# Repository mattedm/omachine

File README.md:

# omachine

The omachine is a linear-rail machine driven by an ODrive S1, controlled by a handheld haptic
handle. Move the handle and the carriage follows. You can also set it running one of 19 stroke
patterns, with the handle showing the speed, length and stroke on its round display. Both boards
are ESP32-S3s, linked wirelessly over ESP-NOW.

This repository has everything: the firmware for both boards, the handle's circuit boards
(KiCad) and the mechanical design (FreeCAD).

## What's here

```
controller/     firmware: the machine's controller (ESP32-S3 dev board, CAN to the ODrive S1)
manipulator/    firmware: the handle (ESP32-S3, DRV8311 gimbal motor driver, display, knob, button)
hardware/
  pcb/
    manipulator/       the handle's main board (KiCad 9)
    encoder-breakouts/ the handle's magnetic and rotary encoder boards (KiCad 9)
  cad/
    manipulator/       the handle (FreeCAD)
    machine/           the main machine (FreeCAD)
docs/           the stroke graph
```

## How it works

- **Start-up.** The controller brings the ODrive into closed loop. It then homes by driving the
  carriage slowly into each end of the rail, and sets the stroke's span just inside them. The
  handle finds its own end stops the same way.
- **Manual.** The carriage follows the handle, updated about 200 times a second. When the
  handle isn't being held, the carriage goes soft so it can be pushed by hand, and the handle's
  motor follows it; it stiffens again once the handle leads.
- **Auto.** The main button switches between Manual and the selected stroke. Pressing the knob
  steps through Speed, Length and Stroke, and turning it changes them. Holding the knob opens
  the menu: Power (the motor's current limit), Save settings (as the start-up defaults),
  Calibrate motor (the handle's), Set up ODrive, Wi-Fi setup and Update firmware.
- **Faults.** If the ODrive stops, the handle shows why ("Supply voltage low", for example),
  what to check and the supply voltage. The controller retries a few times; after that, the
  main button retries.

## Getting started

The FreeCAD files are stored with [Git LFS](https://git-lfs.com/), so install it before cloning:

```
git lfs install
git clone https://github.com/mattedm/omachine.git
```

`controller/` and `manipulator/` are separate ESP-IDF (v6.1) projects. Build and flash each one
from its own folder (`idf.py build`, then `idf.py -p <port> flash`); see each project's README.
In VS Code, open `omachine.code-workspace` rather than the repository folder, so that
IntelliSense uses each project's own build settings.

The two boards talk using `omachine_protocol.h`. Each project has its own copy, and the two
must stay identical. Boards on different protocol versions ignore each other, so always update
both together.

## Firmware updates

After the first flash over USB, both boards update over the air from the handle's
**Update firmware** menu item. It downloads `manipulator.bin` and `controller.bin` from this
repository's latest release, installs its own, and passes the controller's image on over
ESP-NOW. To make a release, tag the repository (e.g. `v1.4`), run
`manipulator/tools/make_release.sh` with ESP-IDF activated, and attach both images to a GitHub
release (the script shows the `gh release create` line).

## The ODrive

The ODrive S1's configuration is in [`controller/odrive/`](controller/odrive). The handle's
**Set up ODrive** menu item writes it to the ODrive over CAN, calibrates the motor (including
anticogging) and saves it. Power 100% is 40 A and the top speed is 15 turns/s. Battery draw is
capped at 20 A, and the ODrive trips below 19 V; both are set for a 6S battery with a 25 A BMS.

## Changing the strokes

Each stroke is a function in [`controller/main/strokes.c`](controller/main/strokes.c). The top
of [`strokes.h`](controller/main/strokes.h) explains how to change one or add a new one. The
handle gets the stroke names from the controller, so only the controller changes.

## Hardware

See [`hardware/`](hardware) for the circuit boards (with the files to order them from JLCPCB)
and the FreeCAD models.

## License

Copyright 2026 MattEdm.

- **Firmware** (`controller/`, `manipulator/`): GPL-3.0-or-later. See [LICENSE](LICENSE). Some
  files carry their own notices; see each project's README.
- **Hardware** (`hardware/`): CERN-OHL-S-2.0. See [hardware/LICENSE](hardware/LICENSE).

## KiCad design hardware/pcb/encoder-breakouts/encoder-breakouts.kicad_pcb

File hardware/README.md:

# omachine hardware

The physical design of the omachine: the circuit board (KiCad) and the mechanical parts (FreeCAD). The firmware is in [`controller/`](../controller) and [`manipulator/`](../manipulator).

| Folder | What | Tool |
|---|---|---|
| [`pcb/manipulator/`](pcb/manipulator) | The handle's board: ESP32-S3-MINI-1, DRV8311 gimbal motor driver, 1S battery charger, connectors for the display, encoder, knob and button | KiCad 9 |
| [`pcb/encoder-breakouts/`](pcb/encoder-breakouts) | The handle's two small boards, on one breakaway panel: the MT6701 magnetic encoder (the handle motor's angle) and the EC11 rotary encoder (the knob) | KiCad 9 |
| [`cad/manipulator/`](cad/manipulator) | The handle: `manipulator.FCStd` | FreeCAD 1.1 |
| [`cad/machine/`](cad/machine) | The main machine: `omachine.FCStd` | FreeCAD 1.1 |

The FreeCAD files are stored with [Git LFS](https://git-lfs.com/). Install it (and run
`git lfs install` once) before cloning, or the `.FCStd` files arrive as small text pointers
instead of models; in a clone made without it, `git lfs pull` fetches them.

## The manipulator board

Open `pcb/manipulator/omachine-manipulator.kicad_pro` in KiCad 9. Its own footprint (USB-C) and
symbols (`jlcpcb.kicad_sym`) are in the project; nearly all 3D models are embedded in the board file.

`pcb/manipulator/production/` has the files to order the current revision from JLCPCB, made with
the Fabrication Toolkit plugin: `omachine_Manipulator_Board_1.2.zip` (Gerbers and drill files),
`bom.csv` and `positions.csv` (for assembly). After changing the board, make them again from the
plugin, so they match.

### Revision 1.2

- R19 and R21 (the main button's sense transistor, Q1) are 10k, not 100k. With 100k, a few
  microamps of leakage from D1 when the board was warm turned Q1 on, and the button read as held.
- Named the omachine manipulator board (was a DRV8311 breakout), with the source link
  github.com/mattedm/omachine on the back silkscreen.

## The encoder boards

Open `pcb/encoder-breakouts/encoder-breakouts.kicad_pro`. The two boards are separate sheets
(`encoder.kicad_sch`, `rotary.kicad_sch`) laid out on one panel with a breakaway rail, and are
ordered together from `pcb/encoder-breakouts/production/` (revision 1.0). They plug into the
manipulator board's ENCODER and ROTARY connectors.

## License

Copyright 2026 MattEdm. The hardware designs in this folder are licensed under the CERN Open
Hardware Licence Version 2 - Strongly Reciprocal (CERN-OHL-S-2.0): see [LICENSE](LICENSE). The
source location is https://github.com/mattedm/omachine. The firmware is under the GPL; see the
top-level [README](../README.md).

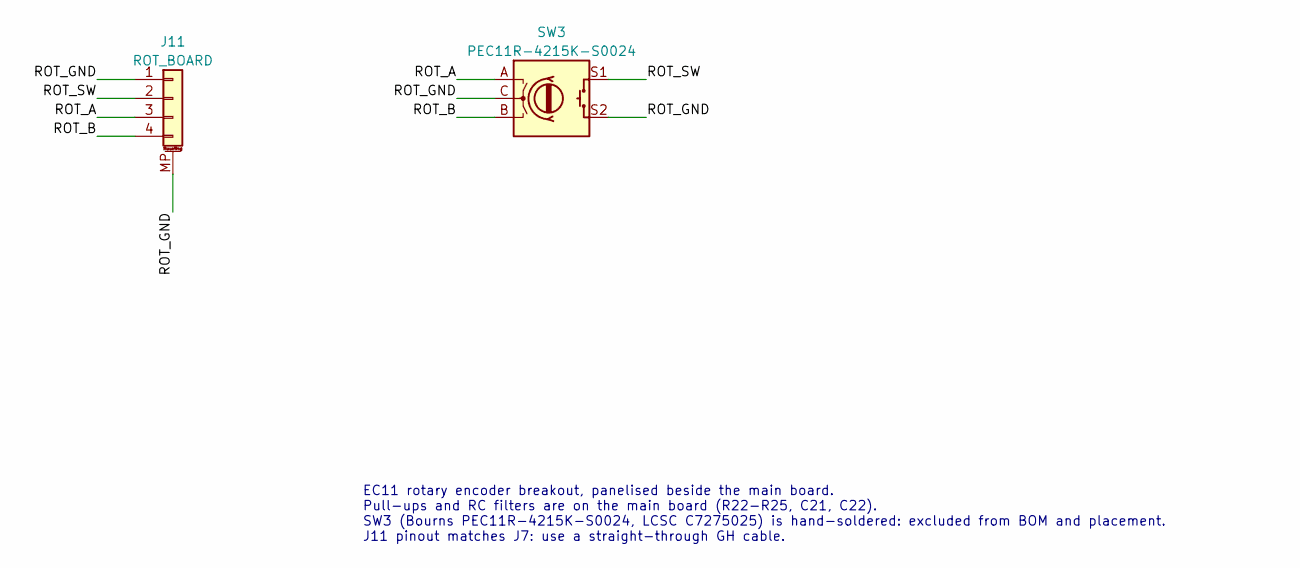
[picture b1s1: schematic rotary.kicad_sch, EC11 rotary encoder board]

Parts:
J11: ROT_BOARD; JST_GH_SM04B-GHS-TB_1x04-1MP_P1.25mm_Horizontal; LCSC Part C51940118
SW3: PEC11R-4215K-S0024; SW-TH_PEC11R-4215K-S0024; LCSC Part C7275025

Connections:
/Rotary/ROT_A: J11.3, SW3.A
/Rotary/ROT_B: J11.4, SW3.B
/Rotary/ROT_GND: J11.1, J11.MP (MountPin), SW3.C, SW3.S2
/Rotary/ROT_SW: J11.2, SW3.S1

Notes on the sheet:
EC11 rotary encoder breakout, panelised beside the main board. Pull-ups and RC filters are on the main board (R22-R25, C21, C22). SW3 (Bourns PEC11R-4215K-S0024, LCSC C7275025) is hand-soldered: excluded from BOM and placement. J11 pinout matches J7: use a straight-through GH cable.

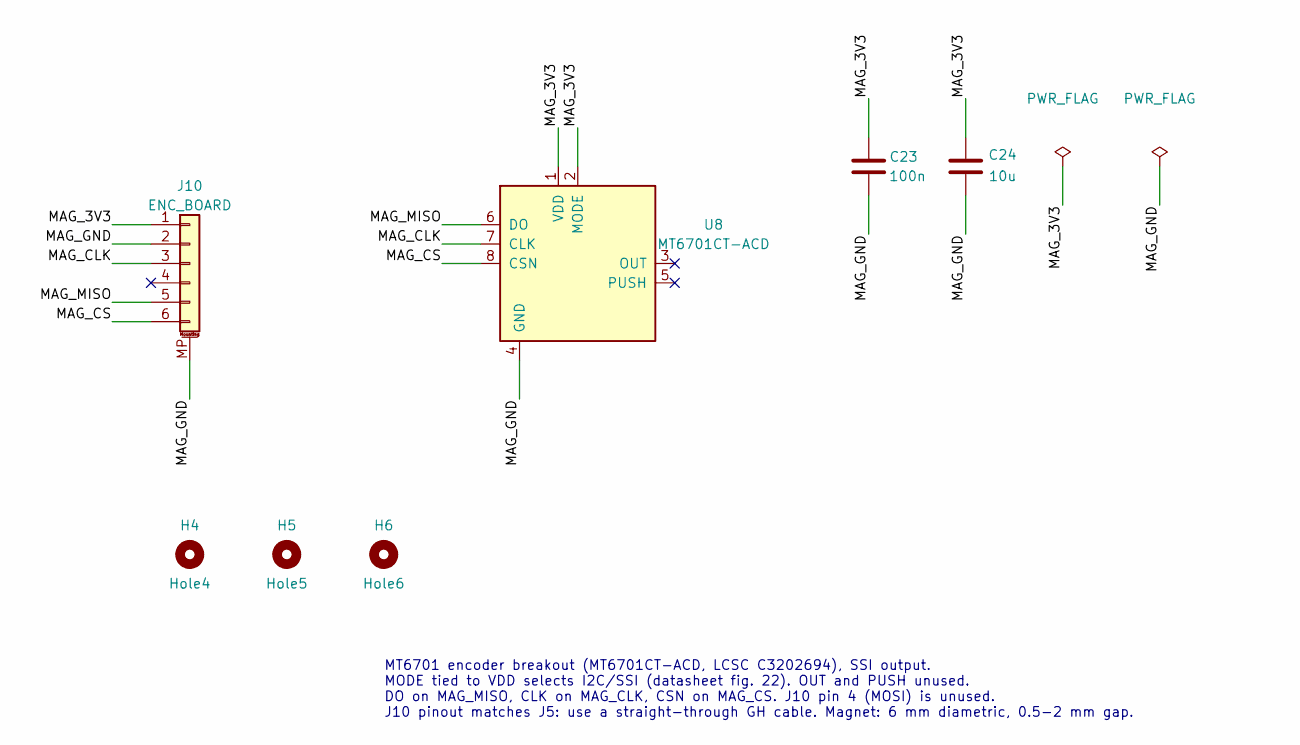
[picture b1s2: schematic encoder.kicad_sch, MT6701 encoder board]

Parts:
C23: 100n; C_0402_1005Metric; LCSC Part C1525
C24: 10u; C_0603_1608Metric; LCSC Part C19702
H4: Hole4; MountingHole_2.1mm_M2_ButtonHead
H5: Hole5; MountingHole_2.1mm_M2_ButtonHead
H6: Hole6; MountingHole_2.1mm_M2_ButtonHead
J10: ENC_BOARD; JST_GH_SM06B-GHS-TB_1x06-1MP_P1.25mm_Horizontal; LCSC Part C388711
U8: MT6701CT-ACD; SOIC-8_3.9x4.9mm_P1.27mm; LCSC Part C3202694

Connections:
/Encoder/MAG_3V3: C23.1, C24.1, J10.1, U8.1 (VDD), U8.2 (MODE)
/Encoder/MAG_CLK: J10.3, U8.7 (CLK)
/Encoder/MAG_CS: J10.6, U8.8 (CSN)
/Encoder/MAG_GND: C23.2, C24.2, J10.2, J10.MP (MountPin), U8.4 (GND)
/Encoder/MAG_MISO: J10.5, U8.6 (DO)

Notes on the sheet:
MT6701 encoder breakout (MT6701CT-ACD, LCSC C3202694), SSI output. MODE tied to VDD selects I2C/SSI (datasheet fig. 22). OUT and PUSH unused. DO on MAG_MISO, CLK on MAG_CLK, CSN on MAG_CS. J10 pin 4 (MOSI) is unused. J10 pinout matches J5: use a straight-through GH cable. Magnet: 6 mm diametric, 0.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

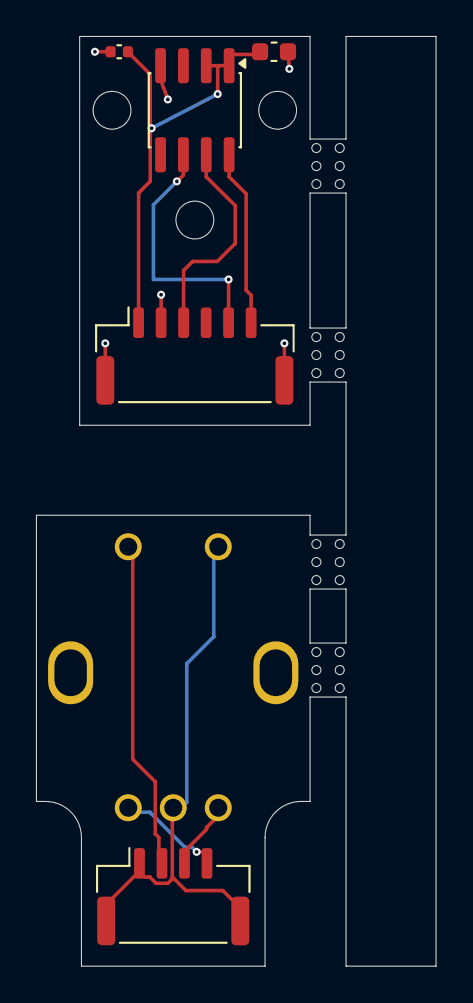
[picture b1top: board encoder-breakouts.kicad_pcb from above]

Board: 2 copper layers, 22.2 x 51.7 mm, 13 parts (1 on the bottom side), 9 nets.

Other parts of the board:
MB1, MB2, MB3, MB4: mousebite

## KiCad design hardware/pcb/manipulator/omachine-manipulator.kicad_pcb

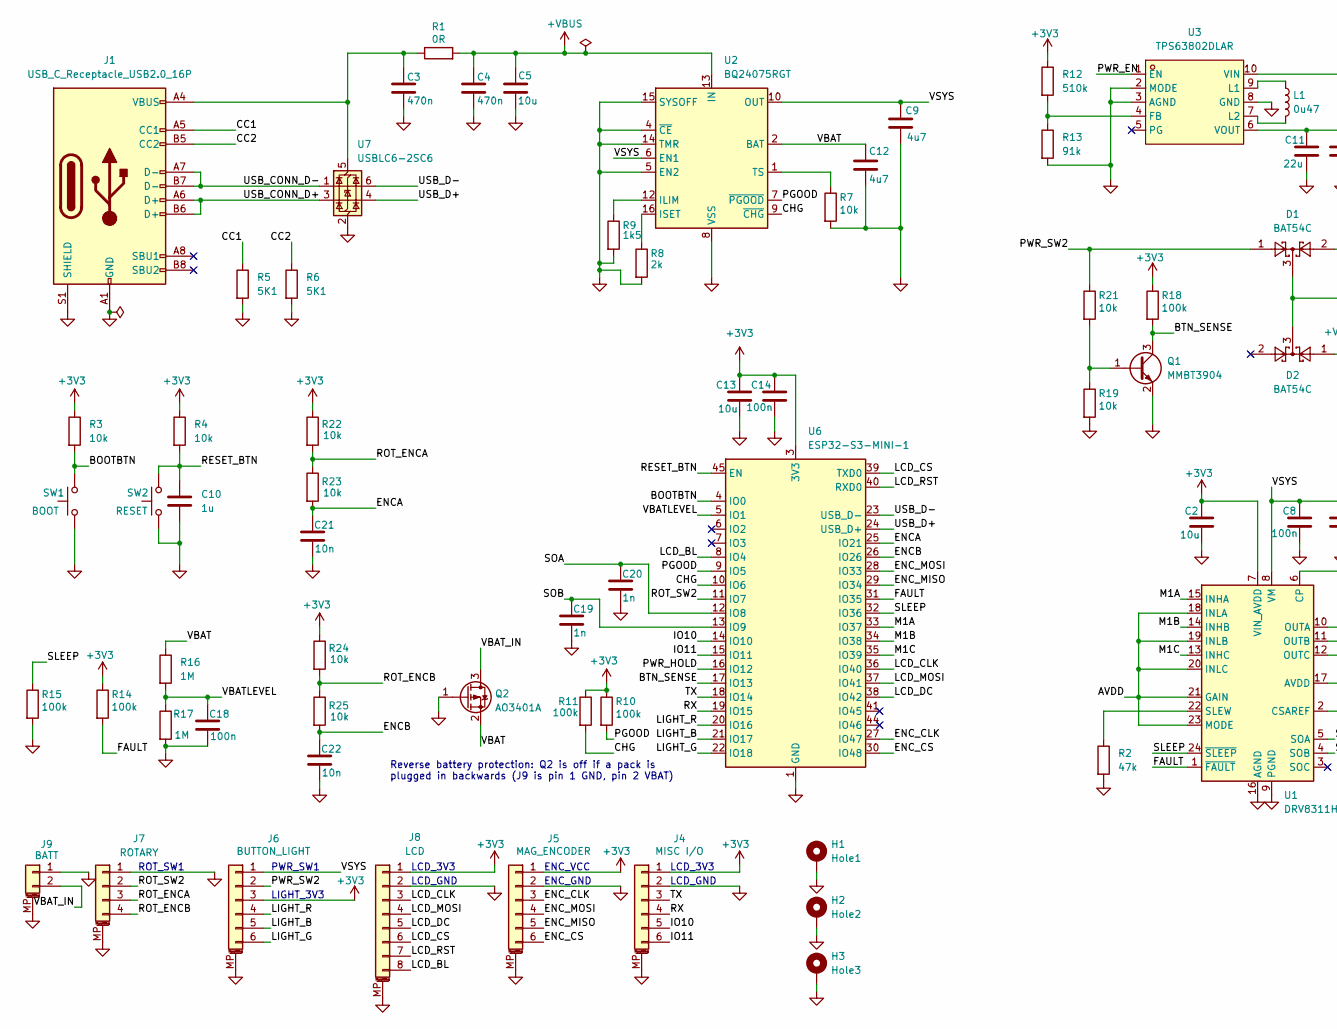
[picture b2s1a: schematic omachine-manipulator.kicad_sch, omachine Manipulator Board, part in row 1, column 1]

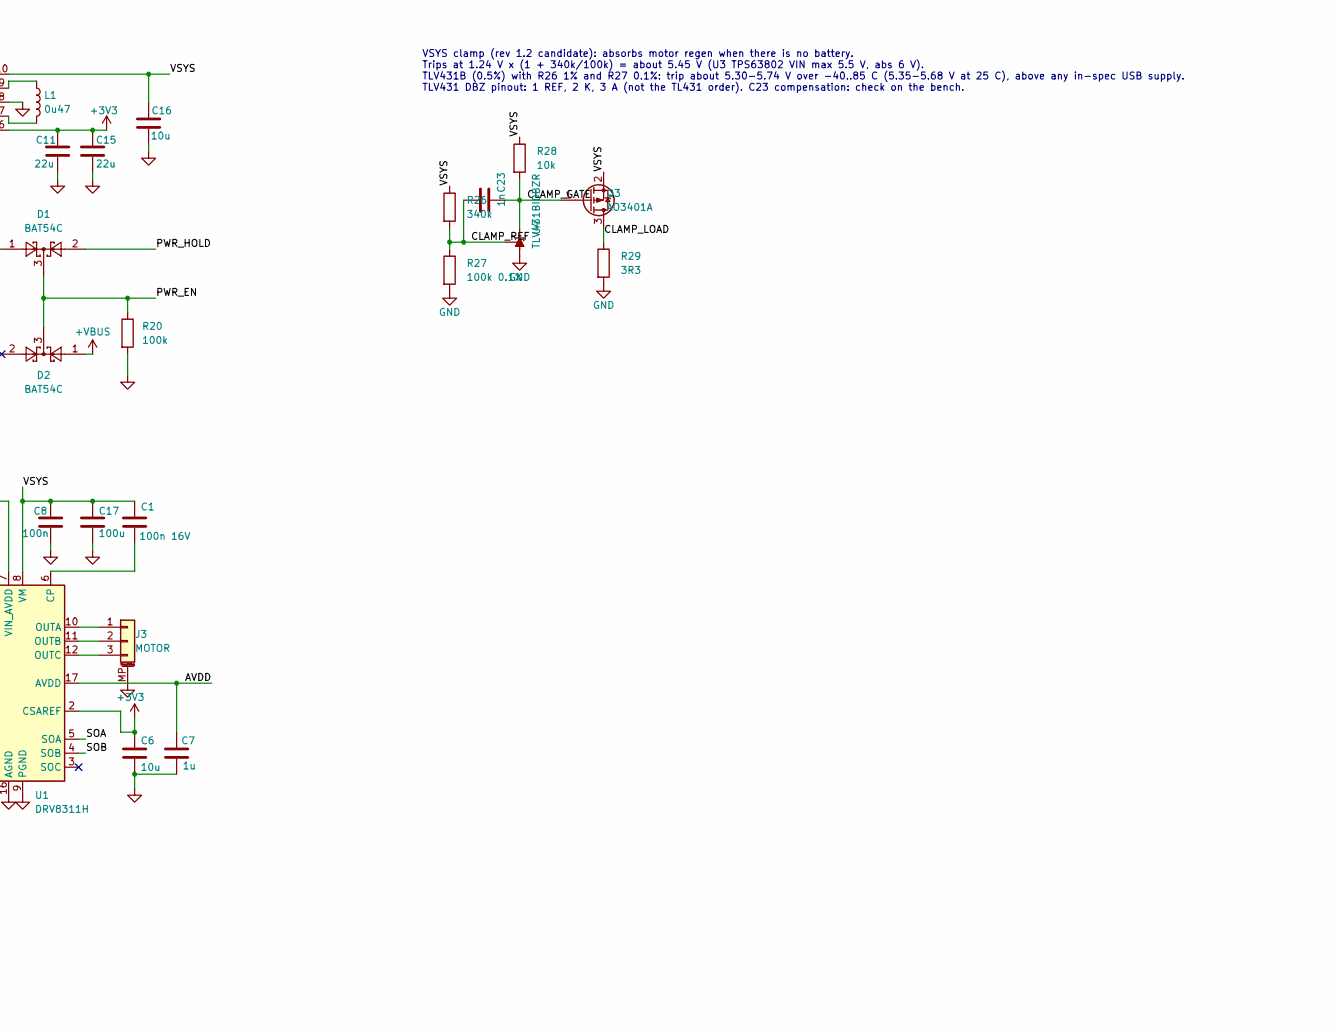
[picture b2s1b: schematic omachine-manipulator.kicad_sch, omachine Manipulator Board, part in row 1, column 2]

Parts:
C1: 100n 16V; C_0402_1005Metric; Manufacturer Part Number CL05B104KO5NNNC; LCSC Part C1525
C2, C5, C6, C13, C16: 10u; C_0805_2012Metric; Manufacturer Part Number CL21A106KAYNNNE; LCSC Part C15850
C3, C4: 470n; C_0402_1005Metric; Manufacturer Part Number CL05A474KP5NNNC; LCSC Part C47339
C7, C10: 1u; C_0402_1005Metric; Manufacturer Part Number CL05A105KA5NQNC; LCSC Part C52923
C8, C14, C18: 100n; C_0402_1005Metric; Manufacturer Part Number CL05B104KO5NNNC; LCSC Part C1525
C9, C12: 4u7; C_0603_1608Metric; Manufacturer Part Number CL10A475KO8NNNC; LCSC Part C19666
C11, C15: 22u; C_0805_2012Metric; Manufacturer Part Number CL21A226MAQNNNE; LCSC Part C45783
C17: 100u; C_1206_3216Metric; Manufacturer Part Number CL31A107MQHNNNE; LCSC Part C15008
C19, C20, C23: 1n; C_0402_1005Metric; Manufacturer Part Number 0402B102K500NT; LCSC Part C1523
C21, C22: 10n; C_0402_1005Metric; Manufacturer Part Number CL05B103KB5NNNC; LCSC Part C15195
D1, D2: BAT54C; SOT-23; Manufacturer Part Number BAT54C,215; LCSC Part C37704
H1: Hole1; MountingHole_2.2mm_M2_Pad
H2: Hole2; MountingHole_2.2mm_M2_Pad
H3: Hole3; MountingHole_2.2mm_M2_Pad
J1: USB_C_Receptacle_USB2.0_16P; USB_C_Receptacle_SHOU_HAN_TYPE-C-16PIN-2MD-073_Horizontal; Manufacturer Part Number TYPE-C 16PIN 2MD(073); LCSC Part C2765186
J3: MOTOR; JST_PH_S3B-PH-SM4-TB_1x03-1MP_P2.00mm_Horizontal; Manufacturer Part Number S3B-PH-SM4-TB(LF)(SN); LCSC Part C265101
J4: MISC I/O; JST_GH_SM06B-GHS-TB_1x06-1MP_P1.25mm_Horizontal; Manufacturer Part Number X1251WRS-06HF-LPSW; LCSC Part C388711
J5: MAG_ENCODER; JST_GH_SM06B-GHS-TB_1x06-1MP_P1.25mm_Horizontal; Manufacturer Part Number X1251WRS-06HF-LPSW; LCSC Part C388711
J6: BUTTON_LIGHT; JST_GH_SM06B-GHS-TB_1x06-1MP_P1.25mm_Horizontal; Manufacturer Part Number X1251WRS-06HF-LPSW; LCSC Part C388711
J7: ROTARY; JST_GH_SM04B-GHS-TB_1x04-1MP_P1.25mm_Horizontal; Manufacturer Part Number XY-SM04B-GHS-TB; LCSC Part C51940118
J8: LCD; JST_GH_SM08B-GHS-TB_1x08-1MP_P1.25mm_Horizontal; Manufacturer Part Number X1251WRS-08HF-LPSW; LCSC Part C388713
J9: BATT; JST_PH_B2B-PH-SM4-TB_1x02-1MP_P2.00mm_Vertical; Manufacturer Part Number B2B-PH-SM4-TB(LF)(SN); LCSC Part C160352
L1: 0u47; L_Changjiang_FNR4015S; Manufacturer Part Number FNR4018SR47NT; LCSC Part C167799
Q1: MMBT3904; SOT-23; Manufacturer Part Number MMBT3904(RANGE:100-300); LCSC Part C20526
Q2, Q3: AO3401A; SOT-23; Manufacturer Part Number AO3401A; LCSC Part C15127
R1: 0R; R_0402_1005Metric; Manufacturer Part Number 0402WGF0000TCE; LCSC Part C17168
R2: 47k; R_0402_1005Metric; Manufacturer Part Number 0402WGF4702TCE; LCSC Part C25792
R3, R4, R7, R19, R21, R22, R23, R24, R25, R28: 10k; R_0402_1005Metric; Manufacturer Part Number 0402WGF1002TCE; LCSC Part C25744
R5, R6: 5K1; R_0402_1005Metric; Manufacturer Part Number 0402WGF5101TCE; LCSC Part C25905
R8: 2k; R_0402_1005Metric; Manufacturer Part Number 0402WGF2001TCE; LCSC Part C4109
R9: 1k5; R_0402_1005Metric; Manufacturer Part Number 0402WGF1501TCE; LCSC Part C25867
R10, R11, R14, R15, R18, R20: 100k; R_0402_1005Metric; Manufacturer Part Number 0402WGF1003TCE; LCSC Part C25741
R12: 510k; R_0402_1005Metric; Manufacturer Part Number 0402WGF5103TCE; LCSC Part C11616
R13: 91k; R_0402_1005Metric; Manufacturer Part Number FRC0402F9102TS; LCSC Part C2909393
R16, R17: 1M; R_0402_1005Metric; Manufacturer Part Number 0402WGF1004TCE; LCSC Part C26083
R26: 340k; R_0402_1005Metric; Manufacturer Part Number AC0402FR-07340KL; LCSC Part C227001
R27: 100k 0.1%; R_0402_1005Metric; Manufacturer Part Number RT0402BRD07100KL; LCSC Part C852472
R29: 3R3; R_0805_2012Metric; Manufacturer Part Number 0805W8J033JT5E; LCSC Part C24787
SW1: BOOT; SW_Push_1P1T_XKB_TS-1187A; Manufacturer Part Number TS-1187A-B-A-B; LCSC Part C318884
SW2: RESET; SW_Push_1P1T_XKB_TS-1187A; Manufacturer Part Number TS-1187A-B-A-B; LCSC Part C318884
U1: DRV8311H; Texas_RRW0024A_WQFN-24-1EP_3x3mm_P0.4mm_EP1.9x1.9mm; Manufacturer Part Number DRV8311HRRWR; LCSC Part C5218862
U2: BQ24075RGT; VQFN-16-1EP_3x3mm_P0.5mm_EP1.6x1.6mm; Manufacturer Part Number BQ24075RGTR; LCSC Part C15464
U3: TPS63802DLAR; VSON-10_L3.0-W2.0-P0.50-TL; MPN TPS63802DLAR; LCSC Part C2845237
U4: TLV431BIDBZR; SOT-23; Manufacturer Part Number TLV431BIDBZR; LCSC Part C398375
U6: ESP32-S3-MINI-1; ESP32-S2-MINI-1; Manufacturer Part Number ESP32-S3-MINI-1-N8; LCSC Part C2913206
U7: USBLC6-2SC6; SOT-23-6; Manufacturer Part Number USBLC6-2SC6; LCSC Part C7519

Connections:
+3V3: C2.1, C6.1, C11.1, C13.1, C14.1, C15.1, J4.1, J5.1, J6.3, J8.1, R3.1, R4.1, R10.1, R11.1, R12.1, R14.1, R18.1, R22.1, R24.1, U1.2 (CSAREF), U1.7 (VIN_AVDD), U3.6 (VOUT), U6.3 (3V3)
+VBUS: C4.1, C5.1, D2.1, R1.2, U2.13 (IN)
/BOOTBTN: R3.2, SW1.2, U6.4 (IO0)
/BTN_SENSE: Q1.3 (C), R18.2, U6.17 (IO13)
/CC1: J1.A5 (CC1), R5.1
/CC2: J1.B5 (CC2), R6.1
/CHG: R11.2, U2.9 (~CHG), U6.10 (IO6)
/CLAMP_GATE: C23.2, Q3.1 (G), R28.2, U4.2 (K)
/CLAMP_LOAD: Q3.3 (D), R29.1
/CLAMP_REF: C23.1, R26.2, R27.1, U4.1 (REF)
/ENCA: C21.1, R23.2, U6.25 (IO21)
/ENCB: C22.1, R25.2, U6.26 (IO26)
/ENC_CLK: J5.3, U6.27 (IO47)
/ENC_CS: J5.6, U6.30 (IO48)
/ENC_MISO: J5.5, U6.29 (IO34)
/ENC_MOSI: J5.4, U6.28 (IO33)
/FAULT: R14.2, U1.1 (~FAULT), U6.31 (IO35)
/IO10: J4.5, U6.14 (IO10)
/IO11: J4.6, U6.15 (IO11)
/LCD_BL: J8.8, U6.8 (IO4)
/LCD_CLK: J8.3, U6.36 (IO40)
/LCD_CS: J8.6, U6.39 (TXD0)
/LCD_DC: J8.5, U6.38 (IO42)
/LCD_MOSI: J8.4, U6.37 (IO41)
/LCD_RST: J8.7, U6.40 (RXD0)
/LIGHT_B: J6.5, U6.21 (IO17)
/LIGHT_G: J6.6, U6.22 (IO18)
/LIGHT_R: J6.4, U6.20 (IO16)
/M1A: U1.15 (INHA), U6.33 (IO37)
/M1B: U1.14 (INHB), U6.34 (IO38)
/M1C: U1.13 (INHC), U6.35 (IO39)
/PGOOD: R10.2, U2.7 (~PGOOD), U6.9 (IO5)
/PWR_EN: D1.3, D2.3, R20.1, U3.1 (EN)
/PWR_HOLD: D1.2, U6.16 (IO12)
/PWR_SW2: D1.1, J6.2, R21.1
/RESET_BTN: C10.1, R4.2, SW2.2, U6.45 (EN)
/ROT_ENCA: J7.3, R22.2, R23.1
/ROT_ENCB: J7.4, R24.2, R25.1
/ROT_SW2: J7.2, U6.11 (IO7)
/RX: J4.4, U6.19 (IO15)
/SLEEP: R15.1, U1.24 (~SLEEP), U6.32 (IO36)
/SOA: C20.1, U1.5 (SOA), U6.12 (IO8)
/SOB: C19.1, U1.4 (SOB), U6.13 (IO9)
/TX: J4.3, U6.18 (IO14)
/USB_CONN_D+: J1.A6 (D+), J1.B6 (D+), U7.3 (I/O2)
/USB_CONN_D-: J1.A7 (D-), J1.B7 (D-), U7.1 (I/O1)
/USB_D+: U6.24 (USB_D+), U7.4 (I/O2)
/USB_D-: U6.23 (USB_D-), U7.6 (I/O1)
/VBAT: C12.2, Q2.2 (E), R16.1, U2.2 (BAT), U2.3 (BAT)
/VBATLEVEL: C18.1, R16.2, R17.1, U6.5 (IO1)
/VBAT_IN: J9.2, Q2.3 (C)
/VSYS: C1.1, C8.1, C9.2, C16.1, C17.1, J6.1, Q3.2 (S), R26.1, R28.1, U1.8 (VM), U2.6 (EN1), U2.10 (OUT), U2.11 (OUT), U3.10 (VIN)
unnamed: J3.1, U1.10 (OUTA)
unnamed: J3.2, U1.11 (OUTB)
unnamed: J3.3, U1.12 (OUTC)
unnamed: Q1.1 (B), R19.1, R21.2
unnamed: C1.2, U1.6 (CP)
unnamed: R2.1, U1.22 (SLEW)
unnamed: R9.1, U2.12 (ILIM)
unnamed: R8.1, U2.16 (ISET)
unnamed: R7.1, U2.1 (TS)
unnamed: R12.2, R13.1, U3.4 (FB)
unnamed: L1.1, U3.9 (L1)
unnamed: L1.2, U3.7 (L2)
unnamed: C3.1, J1.A4 (VBUS), J1.A9 (VBUS), J1.B4 (VBUS), J1.B9 (VBUS), R1.1, U7.5 (VBUS)

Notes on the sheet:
LIGHT_3V3
ENC_GND
ENC_VCC
PWR_SW1
LCD_3V3
LCD_GND
ROT_SW1
Reverse battery protection: Q2 is off if a pack is plugged in backwards (J9 is pin 1 GND, pin 2 VBAT)
VSYS clamp (rev 1.2 candidate): absorbs motor regen when there is no battery. Trips at 1.24 V x (1 + 340k/100k) = about 5.45 V (U3 TPS63802 VIN max 5.5 V, abs 6 V). TLV431B (0.5%) with R26 1% and R27 0.1%: trip about 5.30-5.74 V over -40..85 C (5.35-5.68 V at 25 C), above any in-spec USB supply. TL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

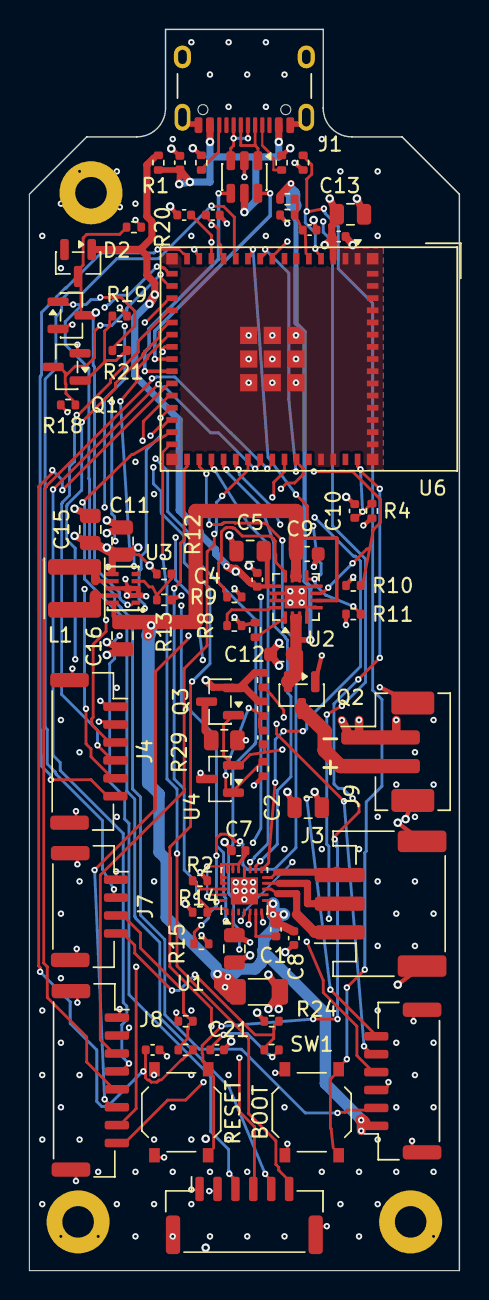
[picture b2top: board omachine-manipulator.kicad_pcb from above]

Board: 4 copper layers, 30.0 x 86.6 mm, 77 parts (0 on the bottom side), 67 nets.

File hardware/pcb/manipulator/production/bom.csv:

Designator,Footprint,Quantity,Value,LCSC Part #
C1,0402,1,100n 16V,C1525
"C10, C7",0402,2,1u,C52923
"C11, C15",0805,2,22u,C45783
"C12, C9",0603,2,4u7,C19666
"C13, C16, C2, C5, C6",0805,5,10u,C15850
"C14, C18, C8",0402,3,100n,C1525
C17,1206,1,100u,C15008
"C19, C20, C23",0402,3,1n,C1523
"C21, C22",0402,2,10n,C15195
"C3, C4",0402,2,470n,C47339
"D1, D2",SOT-23,2,BAT54C,C37704
J1,USB_C_Receptacle_SHOU_HAN_TYPE-C-16PIN-2MD-073_Horizontal,1,USB_C_Receptacle_USB2.0_16P,C2765186
J3,JST_PH_S3B-PH-SM4-TB_1x03-1MP_P2.00mm_Horizontal,1,MOTOR,C265101
J4,JST_GH_SM06B-GHS-TB_1x06-1MP_P1.25mm_Horizontal,1,MISC I/O,C388711
J5,JST_GH_SM06B-GHS-TB_1x06-1MP_P1.25mm_Horizontal,1,MAG_ENCODER,C388711
J6,JST_GH_SM06B-GHS-TB_1x06-1MP_P1.25mm_Horizontal,1,BUTTON_LIGHT,C388711
J7,JST_GH_SM04B-GHS-TB_1x04-1MP_P1.25mm_Horizontal,1,ROTARY,C51940118
J8,JST_GH_SM08B-GHS-TB_1x08-1MP_P1.25mm_Horizontal,1,LCD,C388713
J9,JST_PH_B2B-PH-SM4-TB_1x02-1MP_P2.00mm_Vertical,1,BATT,C160352
L1,L_Changjiang_FNR4015S,1,0u47,C167799
Q1,SOT-23,1,MMBT3904,C20526
"Q2, Q3",SOT-23,2,AO3401A,C15127
R1,0402,1,0R,C17168
"R10, R11, R14, R15, R18, R20",0402,6,100k,C25741
R12,0402,1,510k,C11616
R13,0402,1,91k,C2909393
"R16, R17",0402,2,1M,C26083
"R19, R21, R22, R23, R24, R25, R28, R3, R4, R7",0402,10,10k,C25744
R2,0402,1,47k,C25792
R26,0402,1,340k,C227001
R27,0402,1,100k 0.1%,C852472
R29,0805,1,3R3,C24787
"R5, R6",0402,2,5K1,C25905
R8,0402,1,2k,C4109
R9,0402,1,1k5,C25867
SW1,SW_Push_1P1T_XKB_TS-1187A,1,BOOT,C318884
SW2,SW_Push_1P1T_XKB_TS-1187A,1,RESET,C318884
U1,Texas_RRW0024A_WQFN-24-1EP_3x3mm_P0.4mm_EP1.9x1.9mm,1,DRV8311H,C5218862
U2,VQFN-16-1EP_3x3mm_P0.5mm_EP1.6x1.6mm,1,BQ24075RGT,C15464
U3,VSON-10_L3.0-W2.0-P0.50-TL,1,TPS63802DLAR,C2845237
U4,SOT-23,1,TLV431BIDBZR,C398375
U6,ESP32-S2-MINI-1,1,ESP32-S3-MINI-1,C2913206
U7,SOT-23-6,1,USBLC6-2SC6,C7519

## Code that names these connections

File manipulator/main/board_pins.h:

// SPDX-FileCopyrightText: 2026 MattEdm
// SPDX-License-Identifier: GPL-3.0-or-later
// Pin assignment of the DRV8311 1S battery board: U6, an ESP32-S3-MINI-1-N8 (no PSRAM, so GPIO26 is free).
// Net names are those in drv8311-breakout.kicad_sch.
#pragma once

#include "driver/gpio.h"

// DRV8311H motor driver
#define MOTOR_PWM_A_PIN    GPIO_NUM_37   // M1A -> INHA
#define MOTOR_PWM_B_PIN    GPIO_NUM_38   // M1B -> INHB
#define MOTOR_PWM_C_PIN    GPIO_NUM_39   // M1C -> INHC
#define MOTOR_SLEEP_PIN    GPIO_NUM_36   // SLEEP -> nSLEEP, 100k pull-down: motor off until driven high
#define MOTOR_FAULT_PIN    GPIO_NUM_35   // FAULT <- nFAULT, 100k pull-up
// Low-side current sense outputs (GAIN tied to AVDD: 2 V/A, 0 A at CSAREF/2 = 1.65 V, linear
// 0.25 V to 3.05 V, so about +/-0.7 A). Only valid while that phase's low side is on.
#define MOTOR_SOA_ADC_CHANNEL ADC_CHANNEL_7   // GPIO8: SOA
#define MOTOR_SOB_ADC_CHANNEL ADC_CHANNEL_8   // GPIO9: SOB

// AS5048A magnetic encoder (J5)
#define ENC_CLK_PIN        GPIO_NUM_47
#define ENC_MISO_PIN       GPIO_NUM_34
#define ENC_MOSI_PIN       GPIO_NUM_33
#define ENC_CS_PIN         GPIO_NUM_48

// GC9A01 display (J8). CS and RST are on UART0's pins, so the console must stay on USB
#define LCD_CLK_PIN        GPIO_NUM_40
#define LCD_MOSI_PIN       GPIO_NUM_41
#define LCD_DC_PIN         GPIO_NUM_42
#define LCD_CS_PIN         GPIO_NUM_43
#define LCD_RST_PIN        GPIO_NUM_44
#define LCD_BL_PIN         GPIO_NUM_4    // high = backlight on

// Illuminated power/auto button (J6). The LED's anode is on +3V3, so its pins are active low
#define BUTTON_PIN         GPIO_NUM_13   // BTN_SENSE, low while pressed (Q1, 100k pull-up)
#define BUTTON_LIGHT_R_PIN GPIO_NUM_16
#define BUTTON_LIGHT_G_PIN GPIO_NUM_17
#define BUTTON_LIGHT_B_PIN GPIO_NUM_18

// Rotary encoder (J7). A and B have 10k pull-ups and RC filters on the board; the switch has neither
#define ROTARY_PIN1        GPIO_NUM_21   // ENCA
#define ROTARY_PIN2        GPIO_NUM_26   // ENCB
#define ROTARY_BUTTON_PIN  GPIO_NUM_7    // ROT_SW2, needs the internal pull-up

// Power
#define POWER_HOLD_PIN     GPIO_NUM_12   // PWR_HOLD: high keeps the regulator on when running from the battery
#define USB_POWER_GOOD_PIN GPIO_NUM_5    // PGOOD (BQ24075), low while USB power is valid
#define CHARGE_STATUS_PIN  GPIO_NUM_6    // CHG (BQ24075), low while charging (R11, 100k pull-up)
#define VBAT_ADC_UNIT      ADC_UNIT_1
#define VBAT_ADC_CHANNEL   ADC_CHANNEL_0 // GPIO1: VBATLEVEL, the battery through a 1M/1M divider

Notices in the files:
hardware/pcb/encoder-breakouts/encoder-breakouts.kicad_pcb:
Copyright 2026 MattEdm. CERN-OHL-S-2.0
